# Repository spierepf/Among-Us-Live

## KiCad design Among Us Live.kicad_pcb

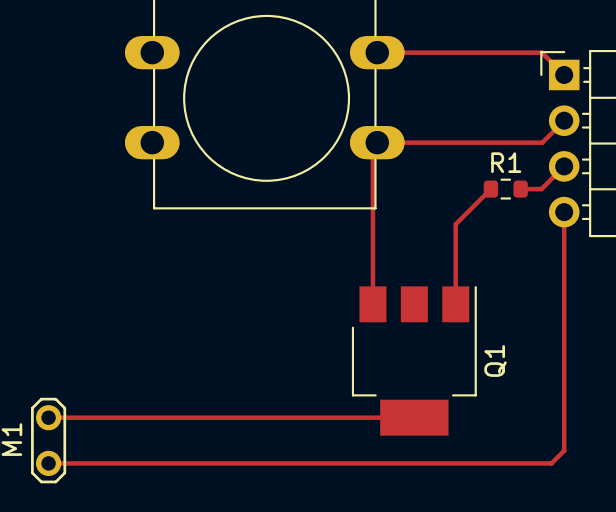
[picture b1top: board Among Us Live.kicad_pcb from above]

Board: 2 copper layers, 5 parts (0 on the bottom side), 6 nets.

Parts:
J1: Conn_01x04_Male; PinHeader_1x04_P2.54mm_Horizontal
M1: Motor_DC; TestPoint_2Pads_Pitch2.54mm_Drill0.8mm
Q1: PZT2222A; SOT-223-3_TabPin2
R1: 1K; R_0603_1608Metric
SW1: SW_Push; SW_PUSH-12mm

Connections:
+3.3V: J1.4, M1.1 (+)
GND: J1.2, Q1.3 (E), SW1.2
unnamed: M1.2 (-), Q1.2 (C)
unnamed: Q1.1 (B), R1.1
unnamed: J1.3, R1.2
unnamed: J1.1, SW1.1
